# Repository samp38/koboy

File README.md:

# Kobo Mini to Flight Computer Kit

## Description
Turn your kobo mini into a complete flight instrument :-)
This project allows you to build an extension card for Kobo which runs XCSoar. The extension card includes a GPS and a pressure sensor. It acts as a sound variometer while it sends data (GPS NMEA data, Vz, temperature, absolute pressure) to XCSoar. In this repo you will find:
- Eagle files and guide to realize the electronic card
- Firmware source (and precompiled hex binaries) for the mcu
- STL parts for the Kobo Mini to receive electronic card (and a bigger battery for long flights)
- XCSoar software for Kobo

### How it works
The GPS chip is standalone. As long as it's powered, it runs and sends NMEA data through its TX output at a given (user definable) frequency. The microntroller manages the pressure sensing and computing: pressure is measured, numerically filtered and derivated at 50Hz to provide Vz. To work with the GPS chip, the microcontroller detects the beginning of the PA6H TX communication and waits the time needed to send variometer data between GPS data bursts. It can seem dubious but it works very well for years in my case. The variometer data sent by the microcontroller to XCSoar mimics a Digifly Leonardo. So you just have to select Digifly Leonardo in XCSoar to have the variometer data read and understood by XCSoar. All the steps of the XCSoar configuration is described in the __software__ part.

### Two versions for two interaction options
To control the sound vario volume and turn the extension card on/off (indeed, you might want to use your Kobo as a reader), there are two possibilities and thus two versions of the PCB:
- "button version": meaningful. Short press to loop in sound levels and long press to turn off.
- "tap-tap version": the button is replaced with a accelerometer which detects the tap. Single tap to loop in sound levels and double tap to turn on/off.

## Hardware

The extension card is based on a [PIC24F16KA101](http://ww1.microchip.com/downloads/en/DeviceDoc/39927c.pdf) microcontroller, a GPS patch antenna chip [(PA6H)](https://cdn-shop.adafruit.com/datasheets/GlobalTop-FGPMMOPA6H-Datasheet-V0A.pdf) and a high resolution pressure sensor [(MS5611)](https://infusionsystems.com/support/MS5611-01BA03.pdf).

The GPS (U5) symbol and footprint come from [Gekkio's KiCad libraries](https://github.com/Gekkio/gekkio-kicad-libs) by Joonas Javanainen, licensed under CC BY 4.0 (copy in `hardware/PCB/Vario Kobo/Button_version/kicad-koboy_button_side/libs/gekkio/`).

## Firmware

Compiled with Microchip XC16 compiler

## Software

XCSoar

## Open issues

### Schematic
- No VDD pin on the programming connector: the PIC must be powered separately while flashing.
- MCLR: the series resistor R2 (100Ω to 470Ω) from the datasheet's reference circuit is missing (C6 100nF sits directly on the MCLR net). It limits the current dumped by the capacitor if the pin breaks down under ESD/EOS (PIC24F16KA102 datasheet, §2.3).
- No local decoupling capacitor on the MAS6240 VIN.
- KOBO_RX is shared between the PIC and the GPS TX (through R5).
- Button version: the MAS6240 EN1/EN2 pins are wired to RA2/RA3, the reverse of `firmware/audio.c` (`EN1 = _RA3`, `EN2 = _RA2`). This dates back to the original Eagle design. As a result the low and medium volume levels are swapped (low gives 2x, medium gives 1x); high and off are unaffected. The taptap version matches the firmware. To be fixed in the firmware with per-version pin definitions.
- R7 (1Ω) in series with the piezo is nearly a jumper: the MAS6240 datasheet suggests an optional 1kΩ to 2kΩ output protection resistor.
- Taptap version: the PIC is programmed through the USB-A plug X1 with a custom pinout (D+ → MCLR, D− → PGC, 5V → PGD, which is also the GPS RX). Plugging the board into a real USB port would put 5V on PGD and the GPS RX.
- Taptap version: the PA6H GND pins 3, 12 and 19 are not connected (Eagle library), only pin 8 is. To be fixed with the Gekkio GPS footprint, as on the button version.

### PCB
- Button version, DRC: 2 silkscreen warnings, no errors: the BZ1 (buzzer) footprint outline from the Eagle import runs over its pads. The fab clips it.
- Taptap version, DRC: 12 errors, all pad-to-pad gaps of 0.195mm (rule 0.2mm) inside the Eagle MMA8452 footprint (0.305mm pads at 0.5mm pitch); to be fixed with a KiCad standard footprint. Silkscreen warnings from the Eagle PA6H and MMA8452 outlines and undersized texts.

### Firmware
- Auto-shutdown after inactivity is not implemented: `vario_shutdown_tick()` counts down but the `shutdown()` call is commented out (`firmware/vario.c`).

### Repository / documentation
- The hardware moved from Eagle to KiCad, with the same structure for both versions (`main` sheet plus a `Power supply` sub-sheet):
  - button version: `hardware/PCB/Vario Kobo/Button_version/kicad-koboy_button_side/main.kicad_pro`;
  - taptap version: `hardware/PCB/Vario Kobo/Taptap_version/kicad-koboy_taptap_side/main.kicad_pro` (migration in progress: references, silkscreen, GPS footprint and pin types still to do).

  The Eagle files are kept for history only; "Vario Kobo TOP" is to be removed.
- The README still says "Eagle files" in the description and needs updating for KiCad.

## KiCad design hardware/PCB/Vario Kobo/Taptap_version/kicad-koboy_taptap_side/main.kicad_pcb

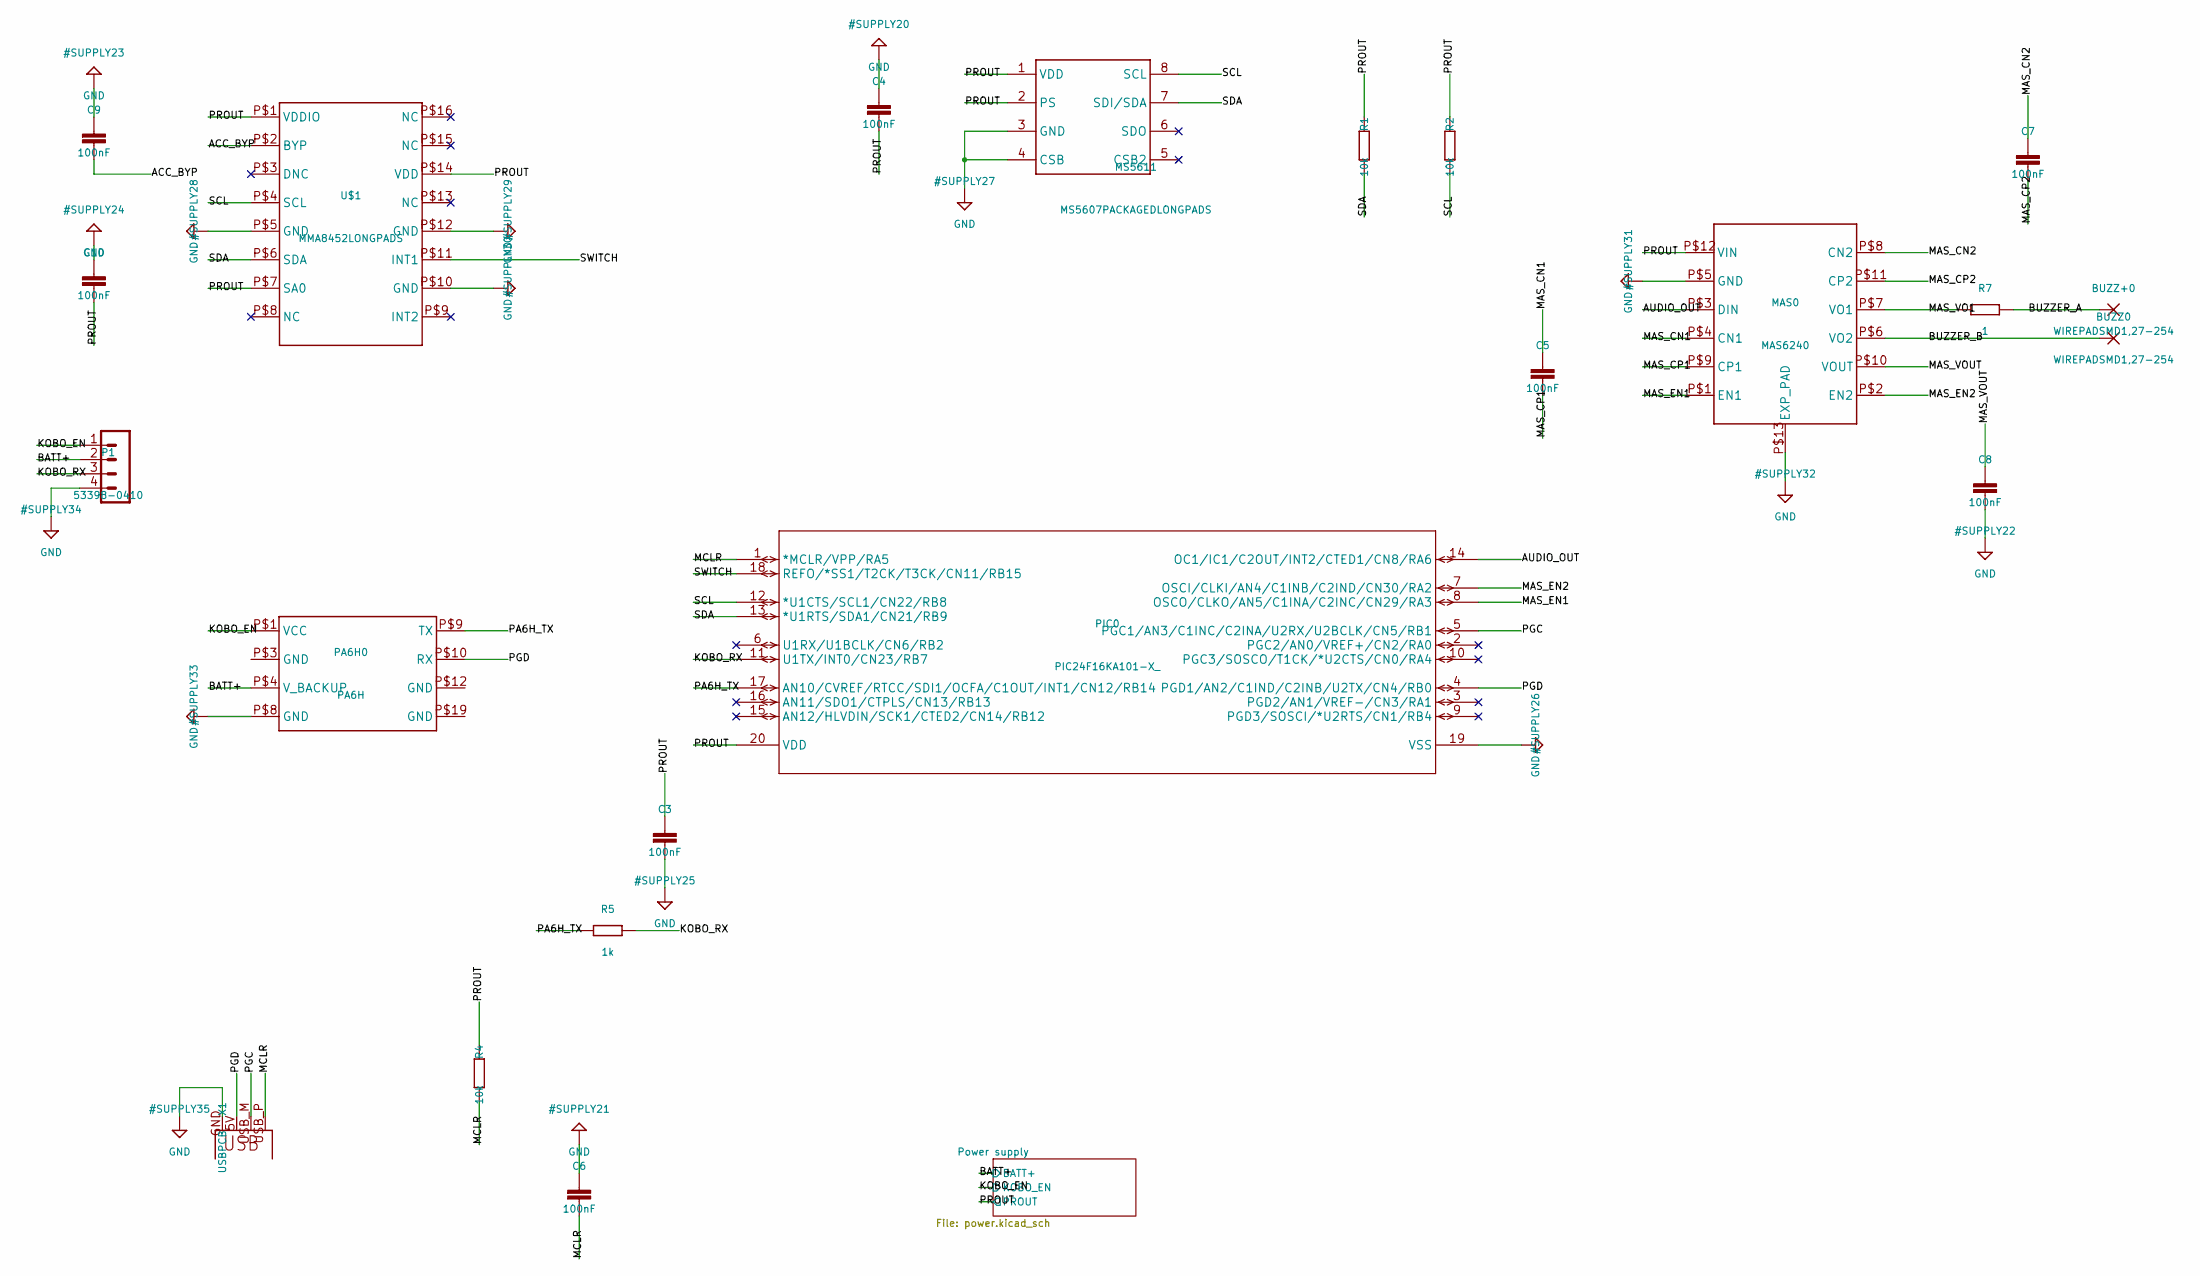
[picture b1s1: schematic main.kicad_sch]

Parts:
BUZZ0: WIREPADSMD1,27-254; SMD1,27-2,54
BUZZ+0: WIREPADSMD1,27-254; SMD1,27-2,54
C3, C4, C5, C6, C7, C8, C9, C10: 100nF; C0603
MAS0: MAS6240; QFN12_3X3_LONGPADS
MS5611: MS5607PACKAGEDLONGPADS; MS5607-02BA03_LONGPADS
P1: 53398-0410
PA6H0: PA6H; PA6H_PRINT
PIC0: PIC24F16KA101-X_; SSOP20_MC
R1, R2, R4: 10k; R0603
R5: 1k; R0603
R7: 1; R0603
U$1: MMA8452LONGPADS; MMA845X_LONG_PADS
X1: USBPCB; USB-A-PCB

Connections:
/ACC_BYP: C9.2, U$1.P$2 (BYP)
/AUDIO_OUT: MAS0.P$3 (DIN), PIC0.14 (OC1/IC1/C2OUT/INT2/CTED1/CN8/RA6)
/BATT+: P1.2, PA6H0.P$4 (V_BACKUP); also elsewhere on the board
/BUZZER_A: BUZZ+0.1 (P_1), R7.1
/BUZZER_B: BUZZ0.1 (P_1), MAS0.P$6 (VO2)
/KOBO_EN: P1.1, PA6H0.P$1 (VCC); also elsewhere on the board
/KOBO_RX: P1.3, PIC0.11 (U1TX/INT0/CN23/RB7), R5.2
/MAS_CN1: C5.1, MAS0.P$4 (CN1)
/MAS_CN2: C7.1, MAS0.P$8 (CN2)
/MAS_CP1: C5.2, MAS0.P$9 (CP1)
/MAS_CP2: C7.2, MAS0.P$11 (CP2)
/MAS_EN1: MAS0.P$1 (EN1), PIC0.8 (OSCO/CLKO/AN5/C1INA/C2INC/CN29/RA3)
/MAS_EN2: MAS0.P$2 (EN2), PIC0.7 (OSCI/CLKI/AN4/C1INB/C2IND/CN30/RA2)
/MAS_VO1: MAS0.P$7 (VO1), R7.2
/MAS_VOUT: C8.1, MAS0.P$10 (VOUT)
/MCLR: C6.2, PIC0.1 (*MCLR/VPP/RA5), R4.1, X1.USB_P (D+)
/PA6H_TX: PA6H0.P$9 (TX), PIC0.17 (AN10/CVREF/RTCC/SDI1/OCFA/C1OUT/INT1/CN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), R5.1
/PGC: PIC0.5 (PGC1/AN3/C1INC/C2INA/U2RX/U2BCLK/CN5/RB1), X1.USB_M (D-)
/PGD: PA6H0.P$10 (RX), PIC0.4 (PGD1/AN2/C1IND/C2INB/U2TX/CN4/RB0), X1.5V (VBUS)
/PROUT: C3.1, C4.2, C10.2, MAS0.P$12 (VIN), MS5611.1 (VDD), MS5611.2 (PS), PIC0.20 (VDD), R1.2, R2.2, R4.2, U$1.P$1 (VDDIO), U$1.P$7 (SA0), U$1.P$14 (VDD); also elsewhere on the board
/SCL: MS5611.8 (SCL), PIC0.12 (*U1CTS/SCL1/CN22/RB8), R2.1, U$1.P$4 (SCL)
/SDA: MS5611.7 (SDI/SDA), PIC0.13 (*U1RTS/SDA1/CN21/RB9), R1.1, U$1.P$6 (SDA)
/SWITCH: PIC0.18 (REFO/*SS1/T2CK/T3CK/CN11/RB15), U$1.P$11 (INT1)
GND: C3.2, C4.1, C6.1, C8.2, C9.1, C10.1, MAS0.P$5 (GND), MAS0.P$13 (EXP_PAD), MS5611.3 (GND), MS5611.4 (CSB), P1.4, PA6H0.P$8 (GND), PIC0.19 (VSS), U$1.P$5 (GND), U$1.P$10 (GND), U$1.P$12 (GND), X1.GND; also elsewhere on the board

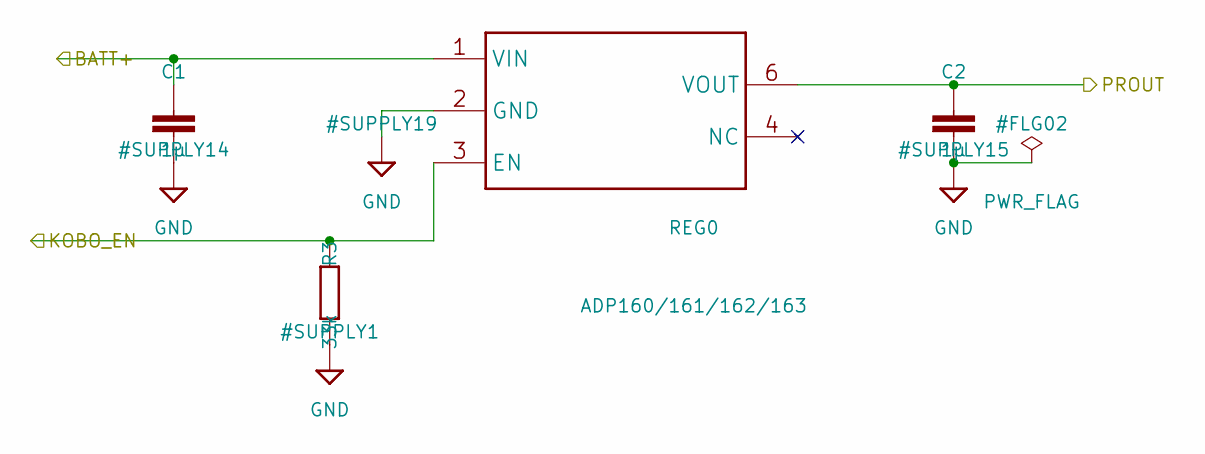
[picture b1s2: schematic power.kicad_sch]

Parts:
C1, C2: 1µ; C0603
R3: 33k; R0603
REG0: ADP160/161/162/163; TSOT23-6_DDC

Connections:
/BATT+: C1.1, REG0.1 (VIN); also elsewhere on the board
/KOBO_EN: R3.2, REG0.3 (EN); also elsewhere on the board
/PROUT: C2.1, REG0.6 (VOUT); also elsewhere on the board
GND: C1.2, C2.2, R3.1, REG0.2 (GND); also elsewhere on the board

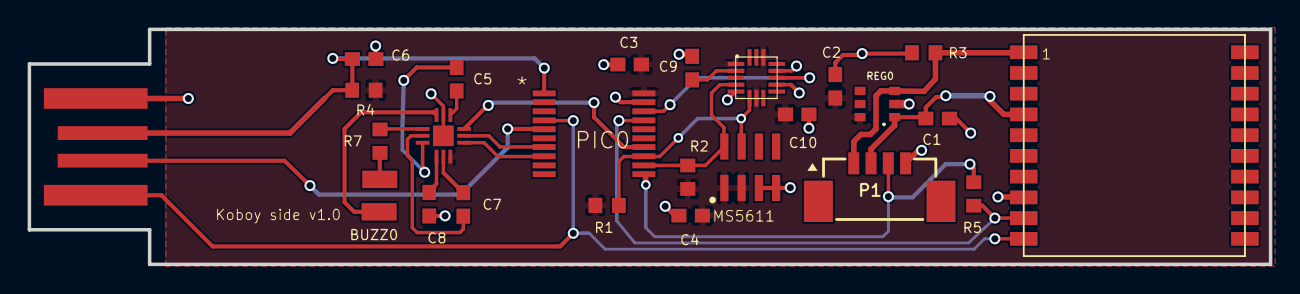
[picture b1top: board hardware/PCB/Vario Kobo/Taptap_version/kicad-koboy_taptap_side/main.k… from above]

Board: 2 copper layers, 89.8 x 17.0 mm, 26 parts (0 on the bottom side), 24 nets.

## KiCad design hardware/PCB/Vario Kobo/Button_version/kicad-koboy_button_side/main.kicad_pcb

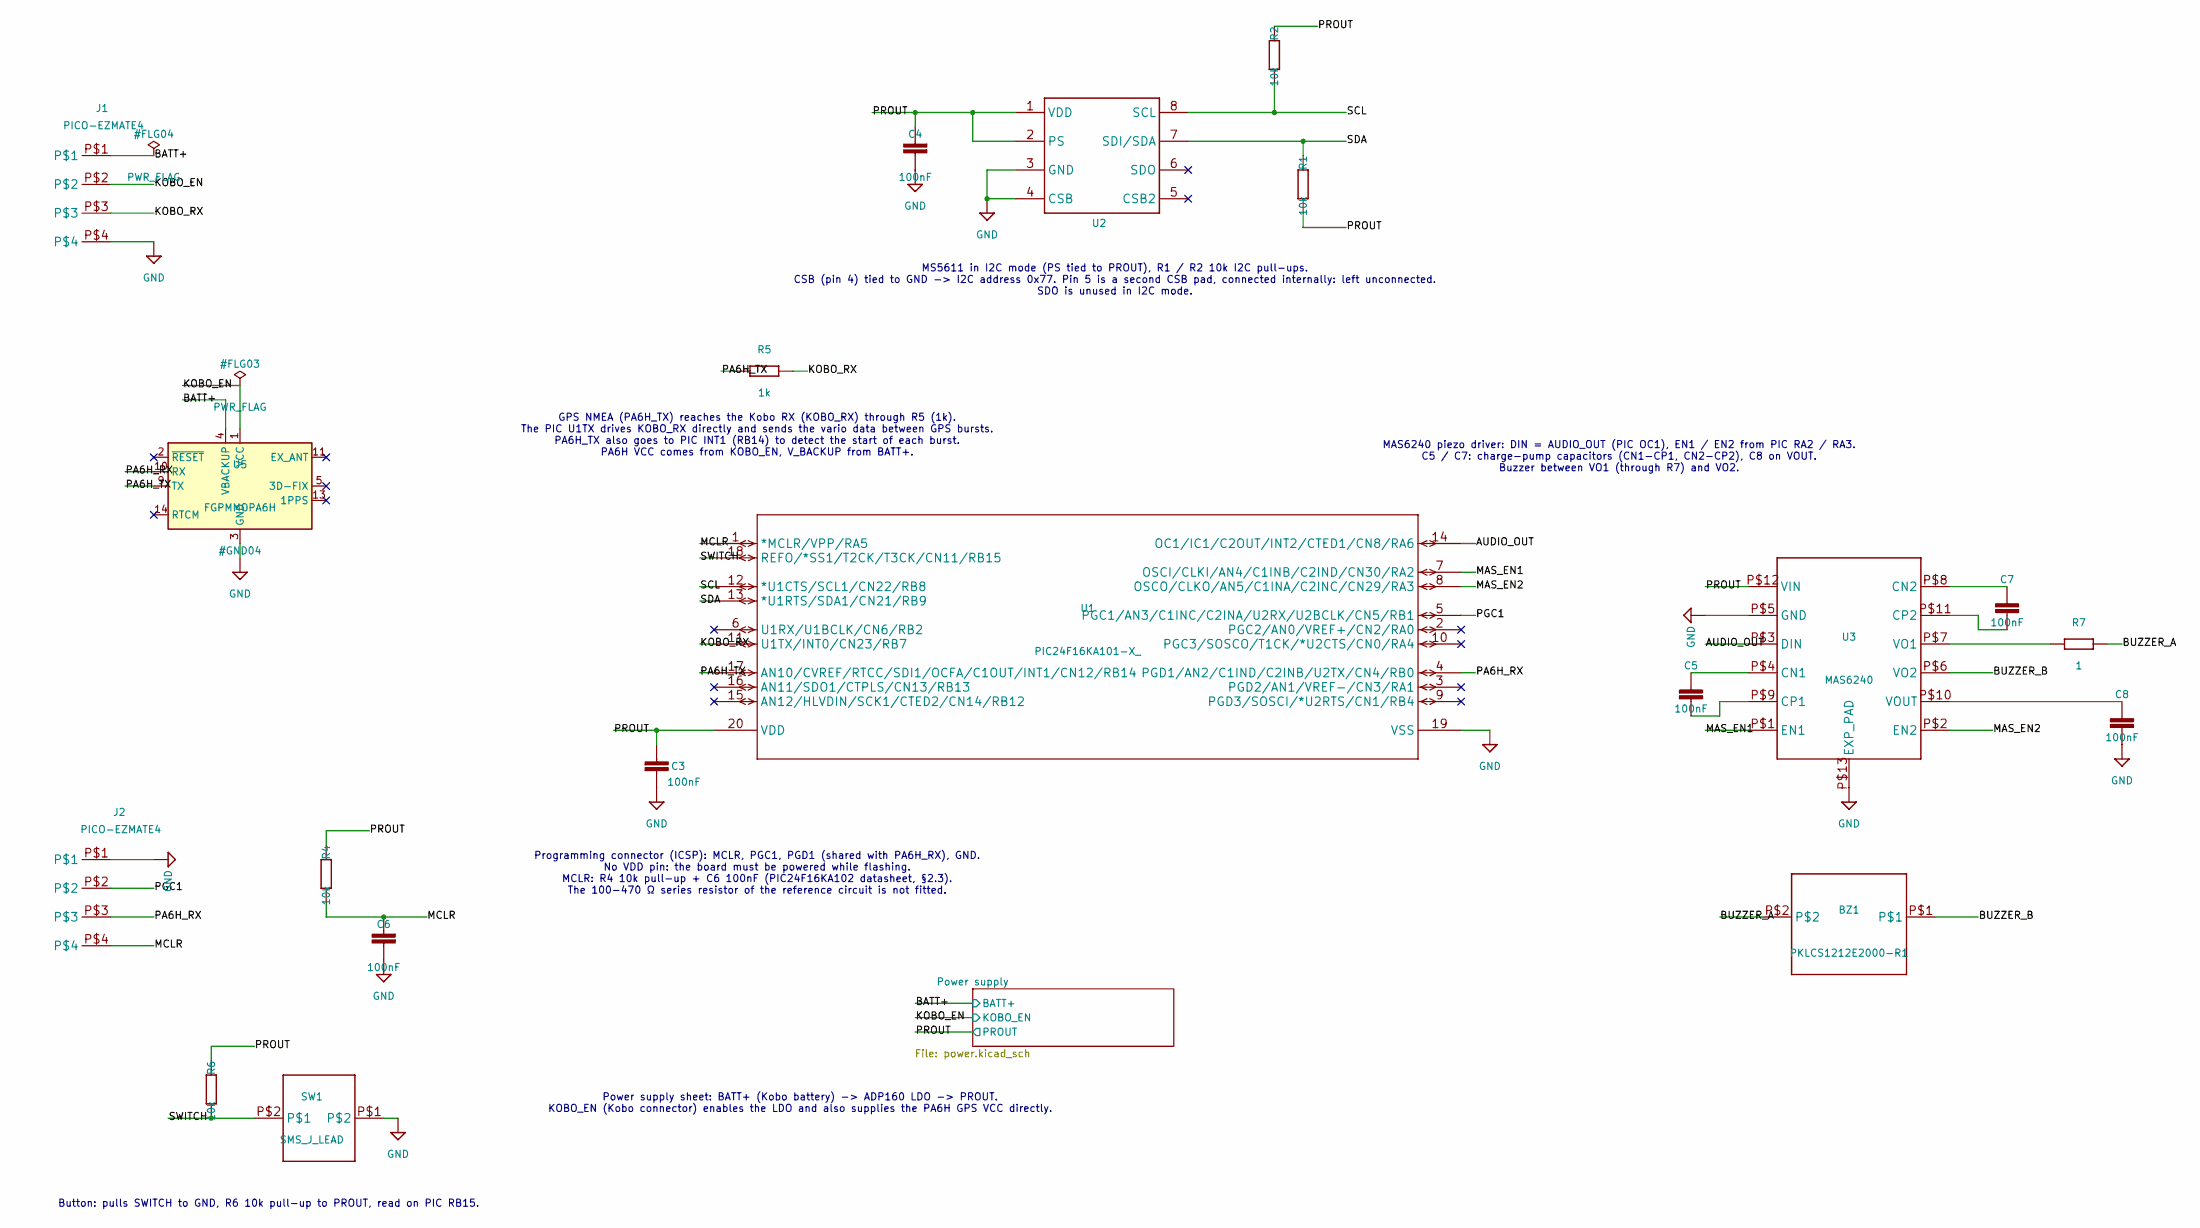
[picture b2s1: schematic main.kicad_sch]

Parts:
BZ1: PKLCS1212E2000-R1; PKLCS1212E2000-R1-SMD
C3, C4, C5, C6, C7, C8: 100nF; C_0603_1608Metric_Pad1.08x0.95mm_HandSolder
J1, J2: PICO-EZMATE4; PICO-EZMATE4-PCB
R1, R2, R4, R6: 10k; R_0603_1608Metric_Pad0.98x0.95mm_HandSolder
R5: 1k; R_0603_1608Metric_Pad0.98x0.95mm_HandSolder
R7: 1; R_0603_1608Metric_Pad0.98x0.95mm_HandSolder
SW1: SMS_J_LEAD
U1: PIC24F16KA101-X_; SSOP20_MC
U2: MS5607PACKAGEDNORMAL; MS5607-02BA03
U3: MAS6240; QFN12_3X3_LONGPADS
U5: FGPMMOPA6H; GlobalTop_FGPMMOPA6H

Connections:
/AUDIO_OUT: U1.14 (OC1/IC1/C2OUT/INT2/CTED1/CN8/RA6), U3.P$3 (DIN)
/BATT+: J1.P$1, U5.4 (VBACKUP); also elsewhere on the board
/BUZZER_A: BZ1.P$2, R7.1
/BUZZER_B: BZ1.P$1, U3.P$6 (VO2)
/KOBO_EN: J1.P$2, U5.1 (VCC); also elsewhere on the board
/KOBO_RX: J1.P$3, R5.2, U1.11 (U1TX/INT0/CN23/RB7)
/MAS_EN1: U1.7 (OSCI/CLKI/AN4/C1INB/C2IND/CN30/RA2), U3.P$1 (EN1)
/MAS_EN2: U1.8 (OSCO/CLKO/AN5/C1INA/C2INC/CN29/RA3), U3.P$2 (EN2)
/MCLR: C6.2, J2.P$4, R4.1, U1.1 (*MCLR/VPP/RA5)
/PA6H_RX: J2.P$3, U1.4 (PGD1/AN2/C1IND/C2INB/U2TX/CN4/RB0), U5.10 (RX)
/PA6H_TX: R5.1, U1.17 (AN10/CVREF/RTCC/SDI1/OCFA/C1OUT/INT1/CN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), U5.9 (TX)
/PGC1: J2.P$2, U1.5 (PGC1/AN3/C1INC/C2INA/U2RX/U2BCLK/CN5/RB1)
/PROUT: C3.1, C4.2, R1.2, R2.2, R4.2, R6.2, U1.20 (VDD), U2.1 (VDD), U2.2 (PS), U3.P$12 (VIN); also elsewhere on the board
/SCL: R2.1, U1.12 (*U1CTS/SCL1/CN22/RB8), U2.8 (SCL)
/SDA: R1.1, U1.13 (*U1RTS/SDA1/CN21/RB9), U2.7 (SDI/SDA)
/SWITCH: R6.1, SW1.P$2, U1.18 (REFO/*SS1/T2CK/T3CK/CN11/RB15)
GND: C3.2, C4.1, C6.1, C8.2, J1.P$4, J2.P$1, SW1.P$1, U1.19 (VSS), U2.3 (GND), U2.4 (CSB), U3.P$5 (GND), U3.P$13 (EXP_PAD), U5.3 (GND), U5.8 (GND), U5.12 (GND), U5.19 (GND); also elsewhere on the board
unnamed: C5.1, U3.P$4 (CN1)
unnamed: C7.1, U3.P$8 (CN2)
unnamed: C5.2, U3.P$9 (CP1)
unnamed: C7.2, U3.P$11 (CP2)
unnamed: R7.2, U3.P$7 (VO1)
unnamed: C8.1, U3.P$10 (VOUT)

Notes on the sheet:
Programming connector (ICSP): MCLR, PGC1, PGD1 (shared with PA6H_RX), GND. No VDD pin: the board must be powered while flashing. MCLR: R4 10k pull-up + C6 100nF (PIC24F16KA102 datasheet, §2.3). The 100-470 Ω series resistor of the reference circuit is not fitted.
MS5611 in I2C mode (PS tied to PROUT), R1 / R2 10k I2C pull-ups. CSB (pin 4) tied to GND -> I2C address 0x77. Pin 5 is a second CSB pad, connected internally: left unconnected. SDO is unused in I2C mode.
Button: pulls SWITCH to GND, R6 10k pull-up to PROUT, read on PIC RB15.
MAS6240 piezo driver: DIN = AUDIO_OUT (PIC OC1), EN1 / EN2 from PIC RA2 / RA3. C5 / C7: charge-pump capacitors (CN1-CP1, CN2-CP2), C8 on VOUT. Buzzer between VO1 (through R7) and VO2.
GPS NMEA (PA6H_TX) reaches the Kobo RX (KOBO_RX) through R5 (1k). The PIC U1TX drives KOBO_RX directly and sends the vario data between GPS bursts. PA6H_TX also goes to PIC INT1 (RB14) to detect the start of each burst. PA6H VCC comes from KOBO_EN, V_BACKUP from BATT+.
Power supply sheet: BATT+ (Kobo battery) -> ADP160 LDO -> PROUT. KOBO_EN (Kobo connector) enables the LDO and also supplies the PA6H GPS VCC directly.

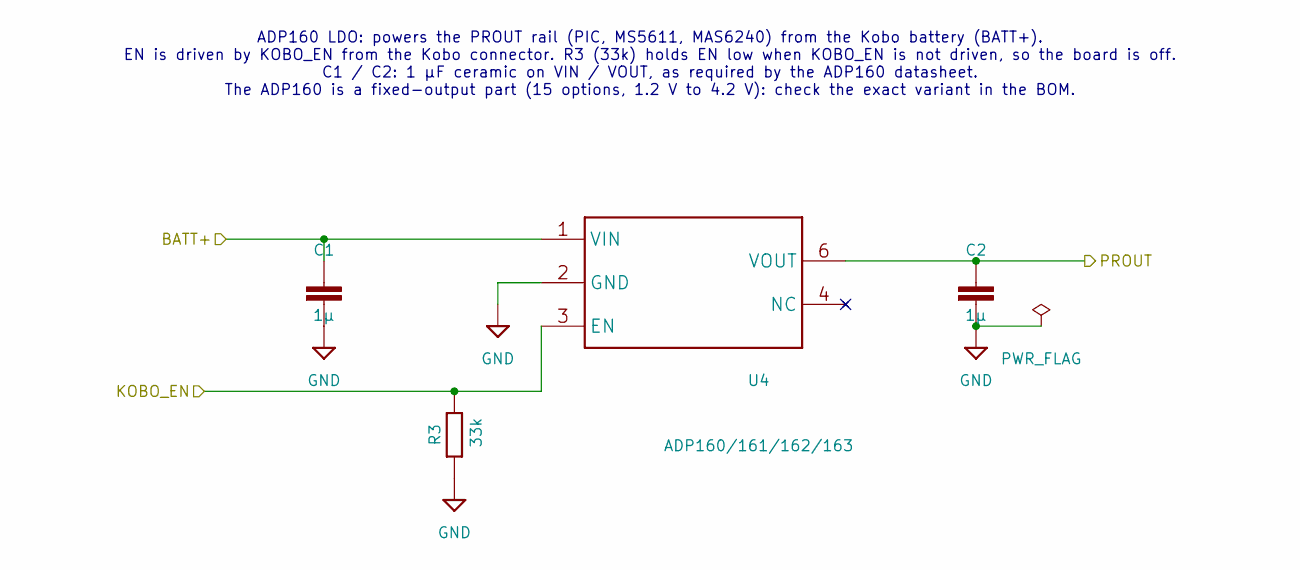
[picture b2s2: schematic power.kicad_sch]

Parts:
C1, C2: 1µ; C_0603_1608Metric_Pad1.08x0.95mm_HandSolder
R3: 33k; R_0603_1608Metric_Pad0.98x0.95mm_HandSolder
U4: ADP160/161/162/163; TSOT23-6_DDC

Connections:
/BATT+: C1.1, U4.1 (VIN); also elsewhere on the board
/KOBO_EN: R3.2, U4.3 (EN); also elsewhere on the board
/PROUT: C2.1, U4.6 (VOUT); also elsewhere on the board
GND: C1.2, C2.2, R3.1, U4.2 (GND); also elsewhere on the board

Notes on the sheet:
ADP160 LDO: powers the PROUT rail (PIC, MS5611, MAS6240) from the Kobo battery (BATT+). EN is driven by KOBO_EN from the Kobo connector. R3 (33k) holds EN low when KOBO_EN is not driven, so the board is off. C1 / C2: 1 µF ceramic on VIN / VOUT, as required by the ADP160 datasheet. The ADP160 is a f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

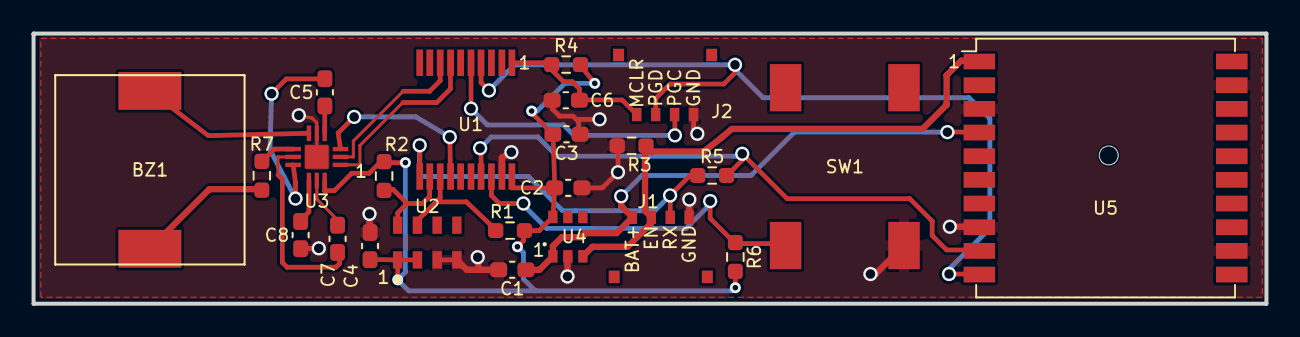
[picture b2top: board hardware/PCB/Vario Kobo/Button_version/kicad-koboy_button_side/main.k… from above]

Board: 2 copper layers, 78.1 x 17.1 mm, 24 parts (0 on the bottom side), 23 nets.

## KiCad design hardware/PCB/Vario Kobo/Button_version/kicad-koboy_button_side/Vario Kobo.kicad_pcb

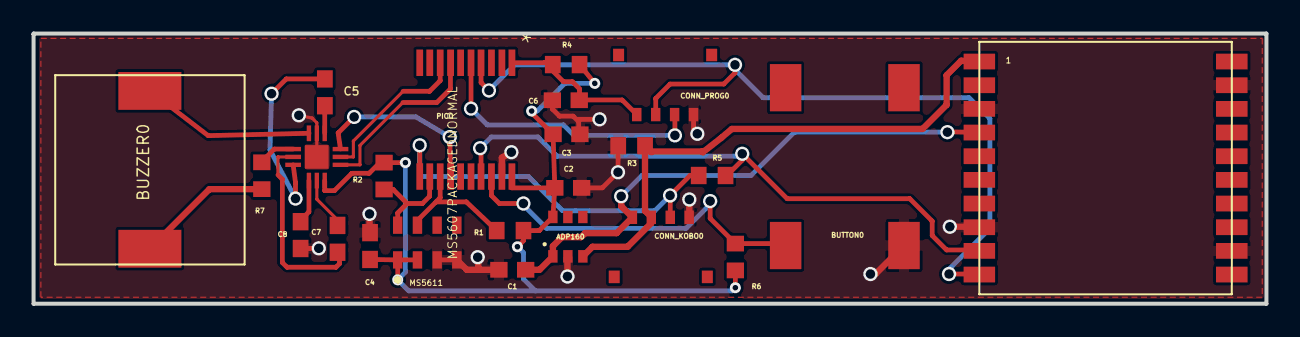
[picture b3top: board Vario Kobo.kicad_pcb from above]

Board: 2 copper layers, 78.1 x 17.1 mm, 24 parts (0 on the bottom side), 23 nets.

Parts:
ADP160: ADP160/161/162/163; TSOT23-6_DDC
BUTTON0: SMS_J_LEAD
BUZZER0: PKLCS1212E2000-R1; PKLCS1212E2000-R1-SMD
C1, C2: 1µ; C0603
C3, C4, C5, C6, C7, C8: 100nF; C0603
CONN_KOBO0: PICO-EZMATE4; PICO-EZMATE4-PCB
CONN_PROG0: PICO-EZMATE4; PICO-EZMATE4-PCB
MAS0: MAS6240; QFN12_3X3_LONGPADS
MS5611: MS5607PACKAGEDNORMAL; MS5607-02BA03
PA6H0: PA6H; PA6H_PRINT
PIC0: PIC24F16KA101-X_; SSOP20_MC
R1, R2, R4, R6: 10k; R0603
R3: 33k; R0603
R5: 1k; R0603
R7: 1; R0603

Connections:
AUDIO_OUT: MAS0.P$3 (DIN), PIC0.14 (OC1/IC1/C2OUT/INT2/CTED1/CN8/RA6)
BATT+: ADP160.1 (VIN), C1.1, CONN_KOBO0.P$1, PA6H0.P$4 (V_BACKUP)
BUZZER_A: BUZZER0.P$2, R7.1
BUZZER_B: BUZZER0.P$1, MAS0.P$6 (VO2)
GND: ADP160.2 (GND), BUTTON0.P$1, C1.2, C2.2, C3.2, C4.1, C6.1, C8.2, CONN_KOBO0.P$4, CONN_PROG0.P$1, MAS0.P$5 (GND), MAS0.P$13 (EXP_PAD), MS5611.3 (GND), MS5611.4 (CSB), PA6H0.P$3 (GND), PA6H0.P$8 (GND), PA6H0.P$12 (GND), PA6H0.P$19 (GND), PIC0.19 (VSS), R3.1
KOBO_EN: ADP160.3 (EN), CONN_KOBO0.P$2, PA6H0.P$1 (VCC), R3.2
KOBO_RX: CONN_KOBO0.P$3, PIC0.11 (U1TX/INT0/CN23/RB7), R5.2
unnamed: C5.1, MAS0.P$4 (CN1)
unnamed: C7.1, MAS0.P$8 (CN2)
unnamed: C5.2, MAS0.P$9 (CP1)
unnamed: C7.2, MAS0.P$11 (CP2)
unnamed: MAS0.P$1 (EN1), PIC0.7 (OSCI/CLKI/AN4/C1INB/C2IND/CN30/RA2)
unnamed: MAS0.P$2 (EN2), PIC0.8 (OSCO/CLKO/AN5/C1INA/C2INC/CN29/RA3)
unnamed: MAS0.P$7 (VO1), R7.2
unnamed: C8.1, MAS0.P$10 (VOUT)
unnamed: MS5611.8 (SCL), PIC0.12 (*U1CTS/SCL1/CN22/RB8), R2.1
unnamed: MS5611.7 (SDI/SDA), PIC0.13 (*U1RTS/SDA1/CN21/RB9), R1.1
unnamed: C6.2, CONN_PROG0.P$4, PIC0.1 (*MCLR/VPP/RA5), R4.1
unnamed: CONN_PROG0.P$2, PIC0.5 (PGC1/AN3/C1INC/C2INA/U2RX/U2BCLK/CN5/RB1)
PA6H_RX: CONN_PROG0.P$3, PA6H0.P$10 (RX), PIC0.4 (PGD1/AN2/C1IND/C2INB/U2TX/CN4/RB0)
PA6H_TX: PA6H0.P$9 (TX), PIC0.17 (AN10/CVREF/RTCC/SDI1/OCFA/C1OUT/INT1/CN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), R5.1
PROUT: ADP160.6 (VOUT), C2.1, C3.1, C4.2, MAS0.P$12 (VIN), MS5611.1 (VDD), MS5611.2 (PS), PIC0.20 (VDD), R1.2, R2.2, R4.2, R6.2
SWITCH: BUTTON0.P$2, PIC0.18 (REFO/*SS1/T2CK/T3CK/CN11/RB15), R6.1

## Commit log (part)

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2016-09-08 First one
    Add Readme
2016-09-08 Add details to README
2016-09-08 Import files
2016-09-08 Correct oscillator frequency comment
2016-09-08 Complete README
2016-09-08 Makefiles and clean some old backups
2016-09-08 clean files
2016-09-09 Clean 3D Files and docs
    Ignoring makefiles
2017-01-23 readme
2017-01-23 réadmet
2018-06-05 cleaning up
2018-06-05 CLEAN
